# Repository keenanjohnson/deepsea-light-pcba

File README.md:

# deepsea-light-pcba
A PCB for controlling Deepsea Lights

| Top | Bottom |
|-----|--------|
|  |  |

The 3D views come from `scripts/render.py`, which drives KiCad's ray tracer
(`kicad-cli pcb render`) and stitches the turntable frames with ffmpeg. The
same script exports the schematic below. The
[Renders workflow](.github/workflows/renders.yml) re-runs it, and the connector
overview, whenever the board or schematic changes and commits the results to
`docs/`.

## Schematic

## Connectors

Rendered automatically by [kicad-callouts](https://github.com/keenanjohnson/kicad-callouts) via GitHub Actions whenever the board changes.

## Fabrication

Generate everything needed to order the board from JLCPCB:

```
scripts/generate_fab.py
```

This writes to `fab/` (gitignored): a flat `*-gerbers.zip` to upload, the same
gerbers and Excellon drill files loose for inspection, a BOM with LCSC part
numbers, a position file for assembly, a schematic PDF, and the DRC/ERC
reports.

The BOM and position file are produced by
[Fabrication-Toolkit](https://github.com/bennymeg/Fabrication-Toolkit), which
applies JLCPCB's part rotation conventions. The script fetches it at a pinned
release into `.fabrication-toolkit/` (gitignored) on first run. It needs a
Python that can import `pcbnew`; on macOS the script finds KiCad's bundled one.
If a part still arrives rotated, add an `FT Rotation Offset` field (degrees,
counter-clockwise) to that symbol and regenerate.

The Pico (U1) and the SparkFun RS-485 breakout (U7) are off-the-shelf modules
that plug into female 2.54 mm headers, so they are excluded from the BOM and
position file. The headers themselves are J1–J4: pad-less footprints
(`Socket_1x*_P2.54mm_NoPads`) placed over the module pin rows, carrying the
LCSC numbers so JLCPCB solders the sockets and the modules are fitted by hand.

J5 is a 4-pole 2.54 mm screw terminal on the right edge carrying I2C1 (GP14
SDA, GP15 SCL) plus 3.3 V and ground, for an external INA238 power monitor
module such as the Adafruit breakout. The firmware expects that sensor at
address 0x40 and tolerates its absence.

Design rule and unrouted-connection errors abort the export. ERC errors are
reported but do not, since the remaining ones are annotation issues such as
missing power flags; pass `--strict` to block on those too. Silkscreen warnings
are expected: several footprint libraries use legend text below JLCPCB's 1.0 mm
minimum height and 0.15 mm minimum stroke.

Order settings that match the design rules in `deepsea-light-pcb.kicad_pro`:
**4 layers, 1.6 mm thick, 1 oz outer copper.** The [Fab files
workflow](.github/workflows/fab.yml) builds the same package in CI and attaches
it to release tags.

## Stackup

| Layer  | Net         | Purpose |
|--------|-------------|---------|
| F.Cu   | `GND`       | Logic ground, 0.1 mm above the signal layer so the PWM input and UART reference a quiet plane |
| In1.Cu | `GND`       | Logic ground, carries most of the signal routing |
| In2.Cu | `+24V`      | Light supply |
| B.Cu   | `LIGHT_GND` | Light return, tightly coupled to the 24 V plane above it |

`GND` and `LIGHT_GND` are deliberately separate on the board. The Pico and the
RS-485 transceiver run from the Navigator's 5 V supply, with 24 V reaching only
the light connectors, following the bench testing in
[CCR_development#34](https://github.com/Seattle-Aquarium/CCR_development/issues/34#issuecomment-4383756606)
that traced light flicker to shared power. There are no ground stitching vias:
JLCPCB does not offer blind or buried vias, so stitching would have to punch
both power planes and put `GND` within clearance of `LIGHT_GND` at every drop.
The two ground pours meet at the through-hole ground pins instead.

The `Power` netclass gives `+24V` and `LIGHT_GND` a 0.5 mm clearance, wider than
the 0.09 mm JLCPCB allows, because those nets land on hand-soldered terminal
blocks where a bridge to the ground pour would put 24 V on the Pico.

### Software Repo

This board is designed to run micropython from this repo: https://github.com/Seattle-Aquarium/CCR_ROV_survey_methods/tree/main/lighting/code

## Random Notes

I usually use this project to get parts / footprints:

https://github.com/TousstNicolas/JLC2KiCad_lib

### Example usage

JLC2KiCadLib C3818565        -dir Deepsea_light_lib            \
                             -model_dir Deepsea_light_dir      \
                             -footprint_lib Deepsea_light_lib  \
                             -symbol_lib_dir Deepsea_light_dir \
                             -symbol_lib Deepsea_light_lib

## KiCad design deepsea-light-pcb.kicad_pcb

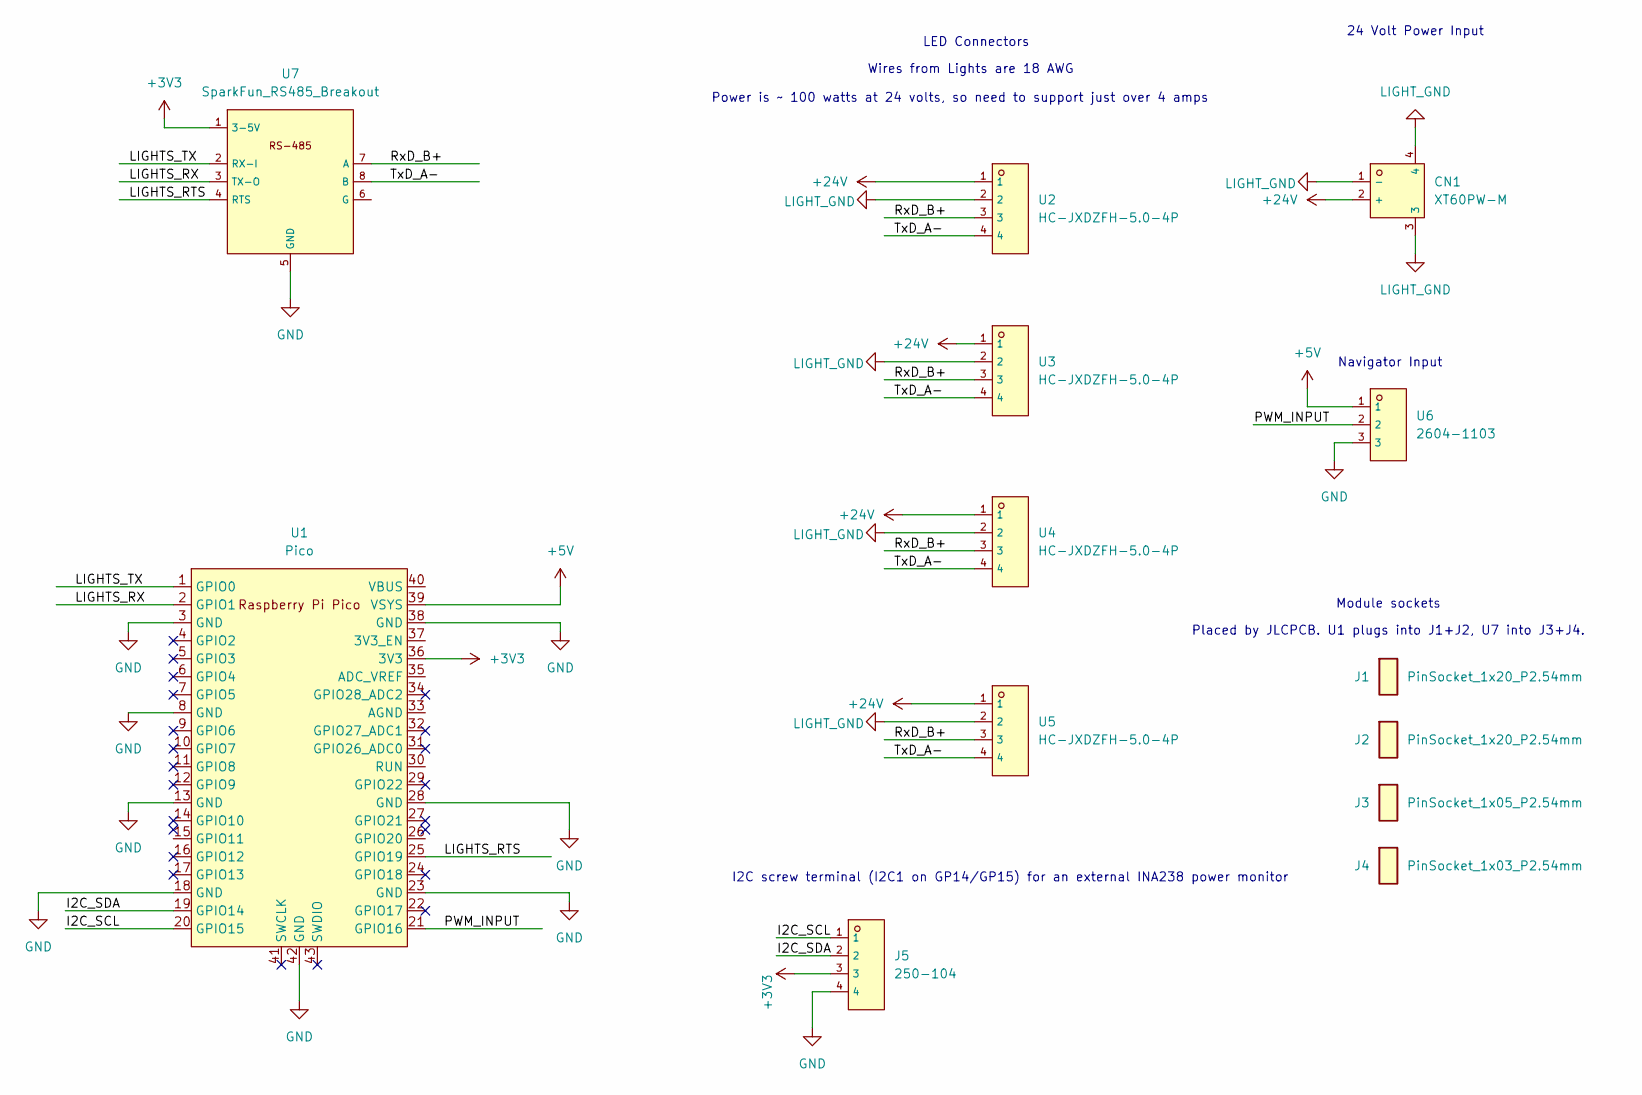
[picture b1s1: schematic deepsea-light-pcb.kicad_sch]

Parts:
CN1: XT60PW-M; CONN-TH_XT60PW-M; LCSC C98732
J1, J2: PinSocket_1x20_P2.54mm; Socket_1x20_P2.54mm_NoPads; LCSC C124410
J3: PinSocket_1x05_P2.54mm; Socket_1x05_P2.54mm_NoPads; LCSC C124414
J4: PinSocket_1x03_P2.54mm; Socket_1x03_P2.54mm_NoPads; LCSC C146690
J5: 250-104; CONN-TH_4P-P3.50_250-104; LCSC C3310053
U1: Pico; RPi_Pico_SMD_TH
U2, U3, U4, U5: HC-JXDZFH-5.0-4P; CONN-TH_2604-1104; LCSC C53454557
U6: 2604-1103; CONN-TH_2604-1103; LCSC C3309758
U7: SparkFun_RS485_Breakout

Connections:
+3V3: J5.3, U1.36 (3V3), U7.1 (3-5V)
+5V: U1.39 (VSYS), U6.1
+24V: CN1.2 (+), U2.1, U3.1, U4.1, U5.1
/I2C_SCL: J5.1, U1.20 (GPIO15)
/I2C_SDA: J5.2, U1.19 (GPIO14)
/LIGHTS_RTS: U1.25 (GPIO19), U7.4 (RTS)
/LIGHTS_RX: U1.2 (GPIO1), U7.3 (TX-O)
/LIGHTS_TX: U1.1 (GPIO0), U7.2 (RX-I)
/PWM_INPUT: U1.21 (GPIO16), U6.2
/RxD_B+: U2.3, U3.3, U4.3, U5.3, U7.7 (A)
/TxD_A-: U2.4, U3.4, U4.4, U5.4, U7.8 (B)
GND: J5.4, U1.3 (GND), U1.8 (GND), U1.13 (GND), U1.18 (GND), U1.23 (GND), U1.28 (GND), U1.38 (GND), U1.42 (GND), U6.3, U7.5 (GND)
LIGHT_GND: CN1.1 (-), CN1.3, CN1.4, U2.2, U3.2, U4.2, U5.2

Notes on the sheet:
24 Volt Power Input
Navigator Input
Module sockets
Placed by JLCPCB. U1 plugs into J1+J2, U7 into J3+J4.
Power is ~ 100 watts at 24 volts, so need to support just over 4 amps
Wires from Lights are 18 AWG
LED Connectors
I2C screw terminal (I2C1 on GP14/GP15) for an external INA238 power monitor

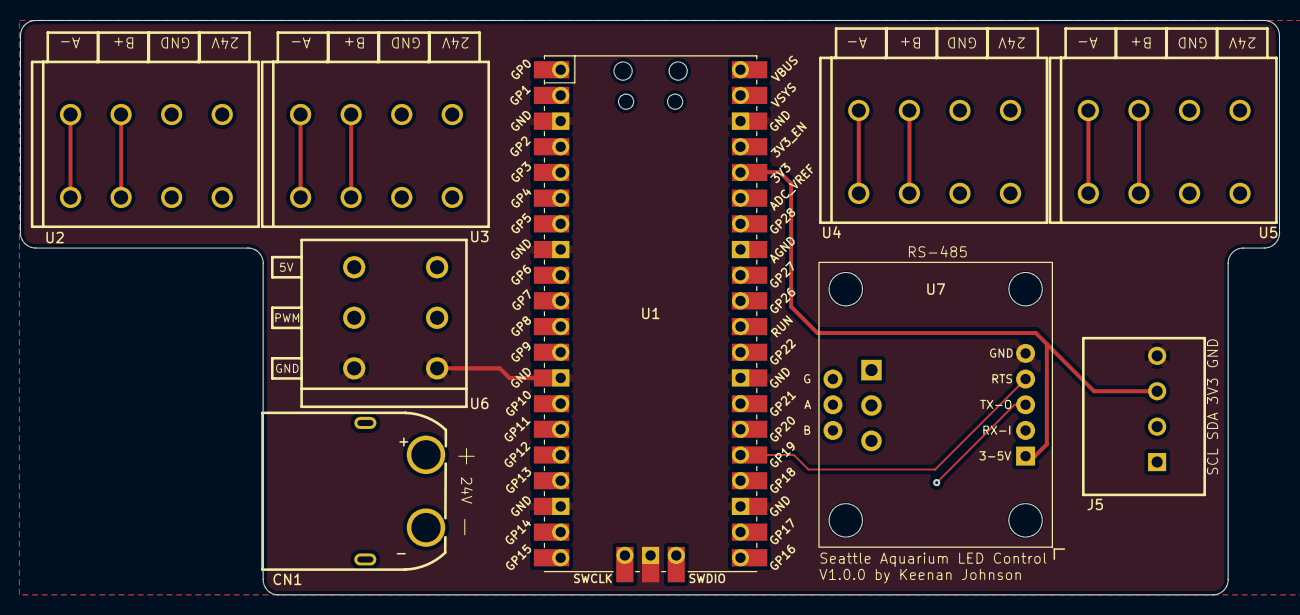
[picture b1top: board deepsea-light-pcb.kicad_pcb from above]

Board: 4 copper layers, 124.5 x 56.8 mm, 13 parts (0 on the bottom side), 13 nets.

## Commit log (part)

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2026-03-18 .gitignore: Add osx files
2026-03-18 Empty project
2026-03-18 Board outline
2026-03-18 Add basic board outline
2026-03-18 Update example
2026-03-19 Add correct pico footprint
2026-03-19 Placement work
2026-05-21 Fix 3d model and update to kicad 10
2026-05-21 More updates to kicad 10
